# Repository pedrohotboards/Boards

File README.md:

Boards
======

This Repo store the electrical design for all the Hotboards created.

Each folder include, electrical desing, layout, gerber files, docs and the 3d models generated, the following structured
should mandatory. In the near future all the boards presented will created.

Boards
  + \CPUs
    + \8-Bits
      + \Microchip
        + pepper-8m.brd
        + pepper-8m.sch
        + \BOM
        + \gerbers
        + \docs
        + \models
      + \Atmel
      + \Freescale
      + \ST
    + \32-bits/USB
    + \32-bits/USB/ETHERNET
    + \32-bits/USB/ETHERNET/DISPLAY
    + \Low-Power
    + \Multimedia
    + \Linux
    + ...
  + \Accesorios
    + \Comunicaciones
      + \USB-Uart
      + ...
  + \Sensores
    + \Temperatura
    + \Acelerometro
    + \Giroscopio
    + \Compass
    + ...
  + \Almacenamiento
    + \Eeprom
    + \Flash
    + \SD
    + ...
  + \Interruptores
    + \Teclado Matricial
    + \Joystick
    + \DIPs
    + ...
  + \Wireless
    + \WiFi
    + \ZigBee
    + \Bluetooth
    + ...
  + \Displays
    + \Leds
    + \RGBs
    + \LCD
    + \OLED
    + \7Segmentos 
    + ...

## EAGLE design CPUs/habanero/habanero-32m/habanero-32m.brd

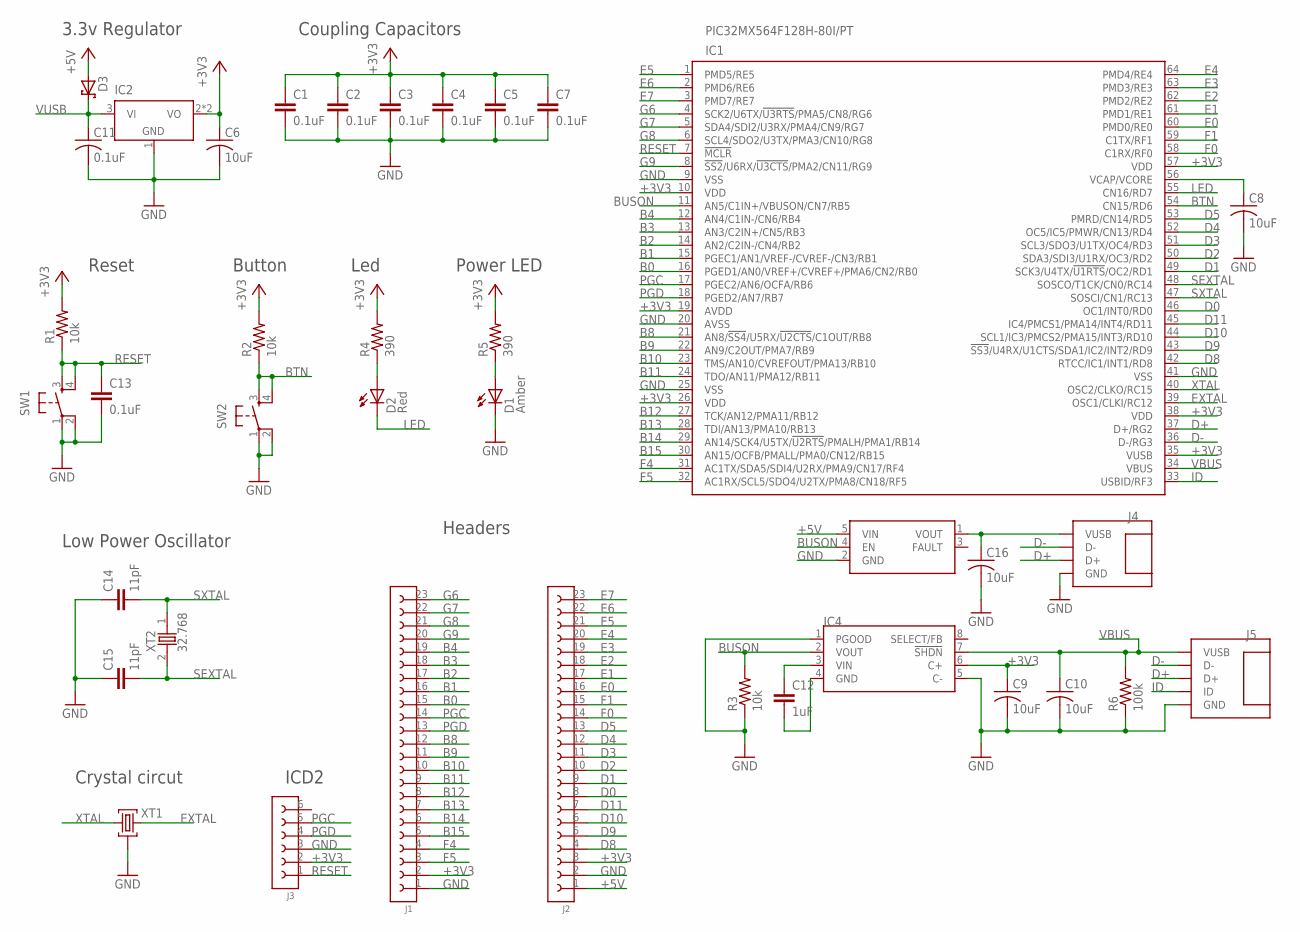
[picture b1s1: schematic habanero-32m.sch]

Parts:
C1, C2, C3, C4, C5, C7, C13: 0.1uF; CAPC0603
C6, C8, C9, C10: 10uF; CAPMP3216-18
C11: 0.1uF; CAPMP3216-18
C12: 1uF; CAPC0805
C14, C15: 11pF; CAPC0603
C16: 10uF; CAPMP3216-18; DIGIKEY 399-8269-2-ND
D1: Amber; D0805
D2: Red; D0805
D3: MBR0530T1G; SOT123160X270-2N
IC1: PIC32MX564F128H-80I/PT; QFP50P1200X1200X100-64N
IC2: LD1117S33TR; SOT230P700X180-4N
IC3: SMTPS2141STR; SOT95P280X100-5M
IC4: MCP1253-33X50I/MS; SOP65P490X109-8M
J1, J2: 61302311121; PHSP254P5842X254X1154-23S
J3: 61300611121; PHSP254P1524X254X1154-6S
J4: 292303-1; USB-A
J5: 1981584-1; USB-MICRO-B
R1, R2, R3: 10k; RESC0603
R4, R5: 390; RESC0603
R6: 100k; RESC0603
SW1, SW2: TL3301NF160QJ; TACT600X600-4J
XT1: AWSCR-12.00CR-C; CERAMIC460X200-3N
XT2: 32.768; CEMIC320X150-2N

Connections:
+3V3: C1.1, C2.1, C3.1, C4.1, C5.1, C6.1, C7.1, C9.1, IC1.10 (VDD), IC1.19 (AVDD), IC1.26 (VDD), IC1.35 (VUSB), IC1.38 (VDD), IC1.57 (VDD), IC2.2 (VO), IC2.4 (VO), IC4.6 (C+), J1.2, J2.3, J3.2, R1.P$2 (2), R2.P$2 (2), R4.P$2 (2), R5.P$2 (2)
+5V: D3.1 (A), IC3.5 (VIN), J2.1
B0: IC1.16 (PGED1/AN0/VREF+/CVREF+/PMA6/CN2/RB0), J1.15
B1: IC1.15 (PGEC1/AN1/VREF-/CVREF-/CN3/RB1), J1.16
B2: IC1.14 (AN2/C2IN-/CN4/RB2), J1.17
B3: IC1.13 (AN3/C2IN+/CN5/RB3), J1.18
B4: IC1.12 (AN4/C1IN-/CN6/RB4), J1.19
B8: IC1.21 (AN8/!SS4!/U5RX/!U2CTS!/C1OUT/RB8), J1.12
B9: IC1.22 (AN9/C2OUT/PMA7/RB9), J1.11
B10: IC1.23 (TMS/AN10/CVREFOUT/PMA13/RB10), J1.10
B11: IC1.24 (TDO/AN11/PMA12/RB11), J1.9
B12: IC1.27 (TCK/AN12/PMA11/RB12), J1.8
B13: IC1.28 (TDI/AN13/PMA10/RB13), J1.7
B14: IC1.29 (AN14/SCK4/U5TX/!U2RTS!/PMALH/PMA1/RB14), J1.6
B15: IC1.30 (AN15/OCFB/PMALL/PMA0/CN12/RB15), J1.5
BTN: IC1.54 (CN15/RD6), R2.P$1 (1), SW2.3 (S), SW2.4 (S1)
BUSON: IC1.11 (AN5/C1IN+/VBUSON/CN7/RB5), IC3.4 (EN), IC4.2 (VOUT), R3.P$2 (2)
D0: IC1.46 (OC1/INT0/RD0), J2.8
D1: IC1.49 (SCK3/U4TX/!U1RTS!/OC2/RD1), J2.9
D2: IC1.50 (SDA3/SDI3/U1RX/OC3/RD2), J2.10
D3: IC1.51 (SCL3/SDO3/U1TX/OC4/RD3), J2.11
D4: IC1.52 (OC5/IC5/PMWR/CN13/RD4), J2.12
D5: IC1.53 (PMRD/CN14/RD5), J2.13
D8: IC1.42 (RTCC/IC1/INT1/RD8), J2.4
D9: IC1.43 (!SS3!/U4RX/U1CTS/SDA1/IC2/INT2/RD9), J2.5
D10: IC1.44 (SCL1/IC3/PMCS2/PMA15/INT3/RD10), J2.6
D11: IC1.45 (IC4/PMCS1/PMA14/INT4/RD11), J2.7
D+: IC1.37 (D+/RG2), J4.2 (D+), J5.3 (D+)
D-: IC1.36 (D-/RG3), J4.3 (D-), J5.2 (D-)
E0: IC1.60 (PMD0/RE0), J2.16
E1: IC1.61 (PMD1/RE1), J2.17
E2: IC1.62 (PMD2/RE2), J2.18
E3: IC1.63 (PMD3/RE3), J2.19
E4: IC1.64 (PMD4/RE4), J2.20
E5: IC1.1 (PMD5/RE5), J2.21
E6: IC1.2 (PMD6/RE6), J2.22
E7: IC1.3 (PMD7/RE7), J2.23
EXTAL: IC1.39 (OSC1/CLKI/RC12), XT1.3
F0: IC1.58 (C1RX/RF0), J2.14
F1: IC1.59 (C1TX/RF1), J2.15
F4: IC1.31 (AC1TX/SDA5/SDI4/U2RX/PMA9/CN17/RF4), J1.4
F5: IC1.32 (AC1RX/SCL5/SDO4/U2TX/PMA8/CN18/RF5), J1.3
G6: IC1.4 (SCK2/U6TX/!U3RTS!/PMA5/CN8/RG6), J1.23
G7: IC1.5 (SDA4/SDI2/U3RX/PMA4/CN9/RG7), J1.22
G8: IC1.6 (SCL4/SDO2/U3TX/PMA3/CN10/RG8), J1.21
G9: IC1.8 (!SS2!/U6RX/!U3CTS!/PMA2/CN11/RG9), J1.20
GND: C1.2, C2.2, C3.2, C4.2, C5.2, C6.2, C7.2, C8.2, C9.2, C10.2, C11.2, C13.2, C14.1, C15.1, C16.2, D1.2 (C), IC1.9 (VSS), IC1.20 (AVSS), IC1.25 (VSS), IC1.41 (VSS), IC2.1 (GND), IC3.2 (GND), IC4.1 (PGOOD), IC4.5 (C-), J1.1, J2.2, J3.3, J4.4 (GND), J5.5 (GND), R3.P$1 (1), R6.P$1 (1), SW1.1, SW1.2 (P1), SW2.1, SW2.2 (P1), XT1.2
ID: IC1.33 (USBID/RF3), J5.4 (ID)
LED: D2.2 (C), IC1.55 (CN16/RD7)
unnamed: C16.1, IC3.1 (VOUT), J4.1 (VUSB)
unnamed: C12.1, IC4.3 (VIN)
unnamed: D1.1 (A), R5.P$1 (1)
unnamed: D2.1 (A), R4.P$1 (1)
unnamed: C12.2, IC4.4 (GND)
unnamed: C8.1, IC1.56 (VCAP/VCORE)
PGC: IC1.17 (PGEC2/AN6/OCFA/RB6), J1.14, J3.5
PGD: IC1.18 (PGED2/AN7/RB7), J1.13, J3.4
RESET: C13.1, IC1.7 (!MCLR), J3.1, R1.P$1 (1), SW1.3 (S), SW1.4 (S1)
SEXTAL: C15.2, IC1.48 (SOSCO/T1CK/CN0/RC14), XT2.2 (1)
SXTAL: C14.2, IC1.47 (SOSCI/CN1/RC13), XT2.1 (2)
VBUS: C10.1, IC1.34 (VBUS), IC4.7 (!SHDN), J5.1 (VUSB), R6.P$2 (2)
VUSB: C11.1, D3.2 (C), IC2.3 (VI)
XTAL: IC1.40 (OSC2/CLKO/RC15), XT1.1

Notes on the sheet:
Coupling Capacitors
3.3v Regulator
Reset
Led
Button
Power LED
Headers
Low Power Oscillator
Crystal circut
ICD2

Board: 2 copper layers, 38 parts (1 on the bottom side), 63 nets, no tracks yet.

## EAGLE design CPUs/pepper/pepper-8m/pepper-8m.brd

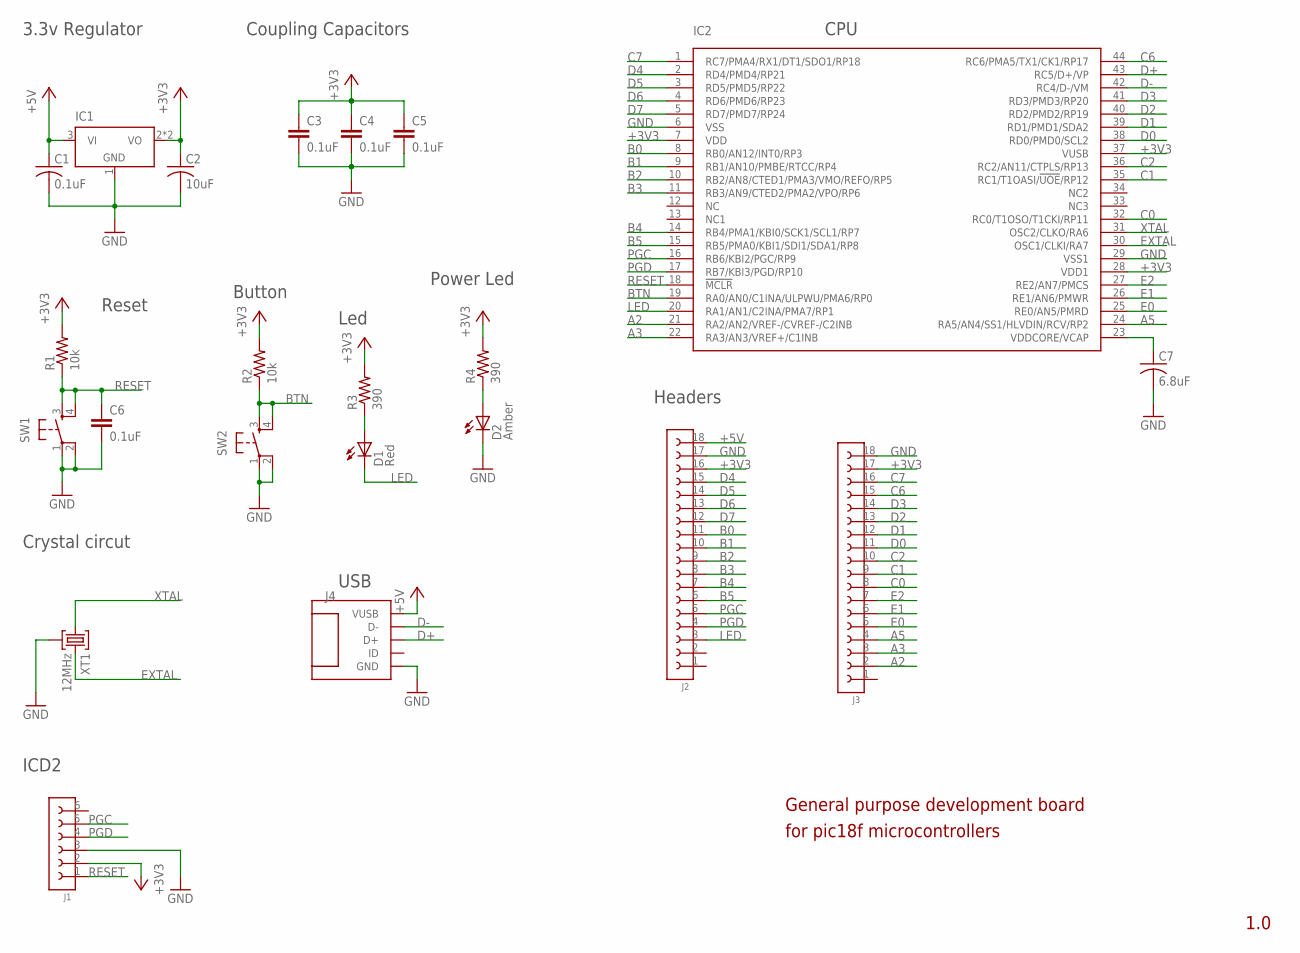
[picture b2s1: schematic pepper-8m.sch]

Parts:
C1: 0.1uF; CAPMP3216-18
C2: 10uF; CAPMP3216-18
C3, C4, C5: 0.1uF; CAPC0603
C6: 0.1uF; CAPC0603; DIGIKEY 399-1100-2-ND
C7: 6.8uF; CAPMP3216-18
D1: Red; D0805
D2: Amber; D0805
IC1: LD1117S33TR; SOT230P700X180-4N
IC2: PIC18F45J50-I/PT'; TQFP80P1200X1200X100-44N
J1: 61300611121; PHSP254P1524X254X1154-6S
J2, J3: 61301811121; PHSP254P4572X254X1154-18S
J4: -1734035-1; USB-MINIB-SMD+SMD+RET
R1, R2: 10k; RESC0603
R3, R4: 390; RESC0603
SW1, SW2: TL3301NF160QJ; TACT600X600-4J
XT1: 12MHz; CERAMIC460X200-3N

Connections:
+3V3: C2.1, C3.1, C4.1, C5.1, IC1.2 (VO), IC1.4 (VO), IC2.7 (VDD), IC2.28 (VDD1), IC2.37 (VUSB), J1.2, J2.16, J3.17, R1.P$2 (2), R2.P$2 (2), R3.P$2 (2), R4.P$2 (2)
+5V: C1.1, IC1.3 (VI), J2.18, J4.1 (VUSB)
A2: IC2.21 (RA2/AN2/VREF-/CVREF-/C2INB), J3.2
A3: IC2.22 (RA3/AN3/VREF+/C1INB), J3.3
A5: IC2.24 (RA5/AN4/SS1/HLVDIN/RCV/RP2), J3.4
B0: IC2.8 (RB0/AN12/INT0/RP3), J2.11
B1: IC2.9 (RB1/AN10/PMBE/RTCC/RP4), J2.10
B2: IC2.10 (RB2/AN8/CTED1/PMA3/VMO/REFO/RP5), J2.9
B3: IC2.11 (RB3/AN9/CTED2/PMA2/VPO/RP6), J2.8
B4: IC2.14 (RB4/PMA1/KBI0/SCK1/SCL1/RP7), J2.7
B5: IC2.15 (RB5/PMA0/KBI1/SDI1/SDA1/RP8), J2.6
BTN: IC2.19 (RA0/AN0/C1INA/ULPWU/PMA6/RP0), R2.P$1 (1), SW2.3 (S), SW2.4 (S1)
C0: IC2.32 (RC0/T1OSO/T1CKI/RP11), J3.8
C1: IC2.35 (RC1/T1OASI/!UOE!/RP12), J3.9
C2: IC2.36 (RC2/AN11/CTPLS/RP13), J3.10
C6: IC2.44 (RC6/PMA5/TX1/CK1/RP17), J3.15
C7: IC2.1 (RC7/PMA4/RX1/DT1/SDO1/RP18), J3.16
D0: IC2.38 (RD0/PMD0/SCL2), J3.11
D1: IC2.39 (RD1/PMD1/SDA2), J3.12
D2: IC2.40 (RD2/PMD2/RP19), J3.13
D3: IC2.41 (RD3/PMD3/RP20), J3.14
D4: IC2.2 (RD4/PMD4/RP21), J2.15
D5: IC2.3 (RD5/PMD5/RP22), J2.14
D6: IC2.4 (RD6/PMD6/RP23), J2.13
D7: IC2.5 (RD7/PMD7/RP24), J2.12
D+: IC2.43 (RC5/D+/VP), J4.3 (D+)
D-: IC2.42 (RC4/D-/VM), J4.2 (D-)
E0: IC2.25 (RE0/AN5/PMRD), J3.5
E1: IC2.26 (RE1/AN6/PMWR), J3.6
E2: IC2.27 (RE2/AN7/PMCS), J3.7
EXTAL: IC2.30 (OSC1/CLKI/RA7), XT1.3
GND: C1.2, C2.2, C3.2, C4.2, C5.2, C6.2, C7.2, D2.2 (C), IC1.1 (GND), IC2.6 (VSS), IC2.29 (VSS1), J1.3, J2.17, J3.18, J4.5 (GND), SW1.1, SW1.2 (P1), SW2.1, SW2.2 (P1), XT1.2
LED: D1.2 (C), IC2.20 (RA1/AN1/C2INA/PMA7/RP1), J2.3
unnamed: D1.1 (A), R3.P$1 (1)
unnamed: C7.1, IC2.23 (VDDCORE/VCAP)
unnamed: D2.1 (A), R4.P$1 (1)
PGC: IC2.16 (RB6/KBI2/PGC/RP9), J1.5, J2.5
PGD: IC2.17 (RB7/KBI3/PGD/RP10), J1.4, J2.4
RESET: C6.1, IC2.18 (!MCLR), J1.1, R1.P$1 (1), SW1.3 (S), SW1.4 (S1)
XTAL: IC2.31 (OSC2/CLKO/RA6), XT1.1

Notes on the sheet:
General purpose development board
3.3v Regulator
Crystal circut
CPU
Reset
Led
Button
USB
Headers
ICD2
Coupling Capacitors
1.0
for pic18f microcontrollers
Power Led

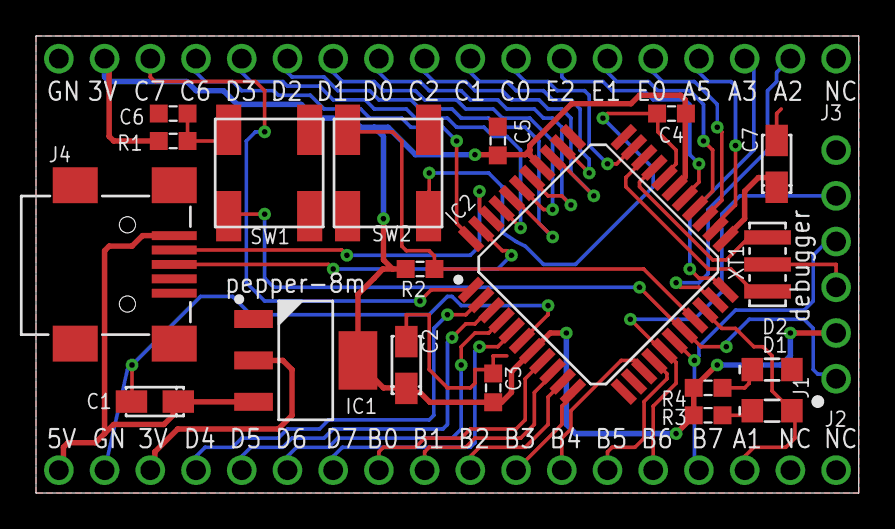
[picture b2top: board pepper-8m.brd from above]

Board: 2 copper layers, 45.7 x 25.4 mm, 22 parts (0 on the bottom side), 40 nets.

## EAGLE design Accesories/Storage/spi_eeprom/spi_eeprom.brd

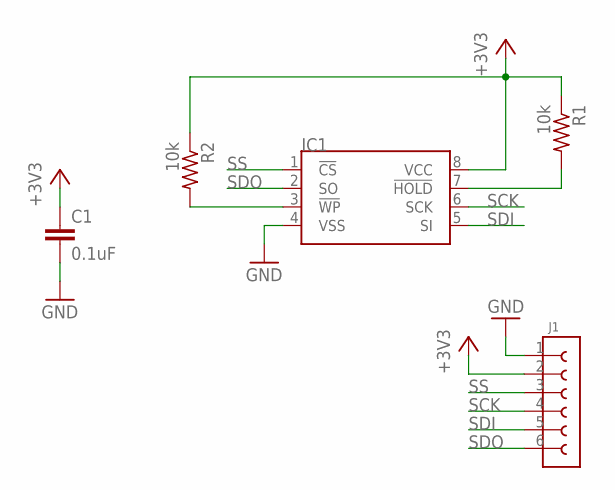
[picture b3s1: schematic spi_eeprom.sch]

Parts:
C1: 0.1uF; CAPC0603
IC1: 25LC320A-I/SN; SOIC127P600X175-8N
J1: 61300611121; PHSP254P1524X254X1154-6S
R1, R2: 10k; RESC0603

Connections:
+3V3: C1.1, IC1.8 (VCC), J1.2, R1.P$1 (1), R2.P$1 (1)
GND: C1.2, IC1.4 (VSS), J1.1
unnamed: IC1.3 (!WP), R2.P$2 (2)
unnamed: IC1.7 (!HOLD), R1.P$2 (2)
SCK: IC1.6 (SCK), J1.4
SDI: IC1.5 (SI), J1.5
SDO: IC1.2 (SO), J1.6
SS: IC1.1 (!CS), J1.3

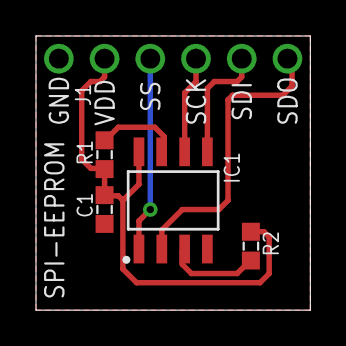
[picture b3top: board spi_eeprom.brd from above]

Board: 2 copper layers, 15.2 x 15.2 mm, 5 parts (0 on the bottom side), 8 nets.

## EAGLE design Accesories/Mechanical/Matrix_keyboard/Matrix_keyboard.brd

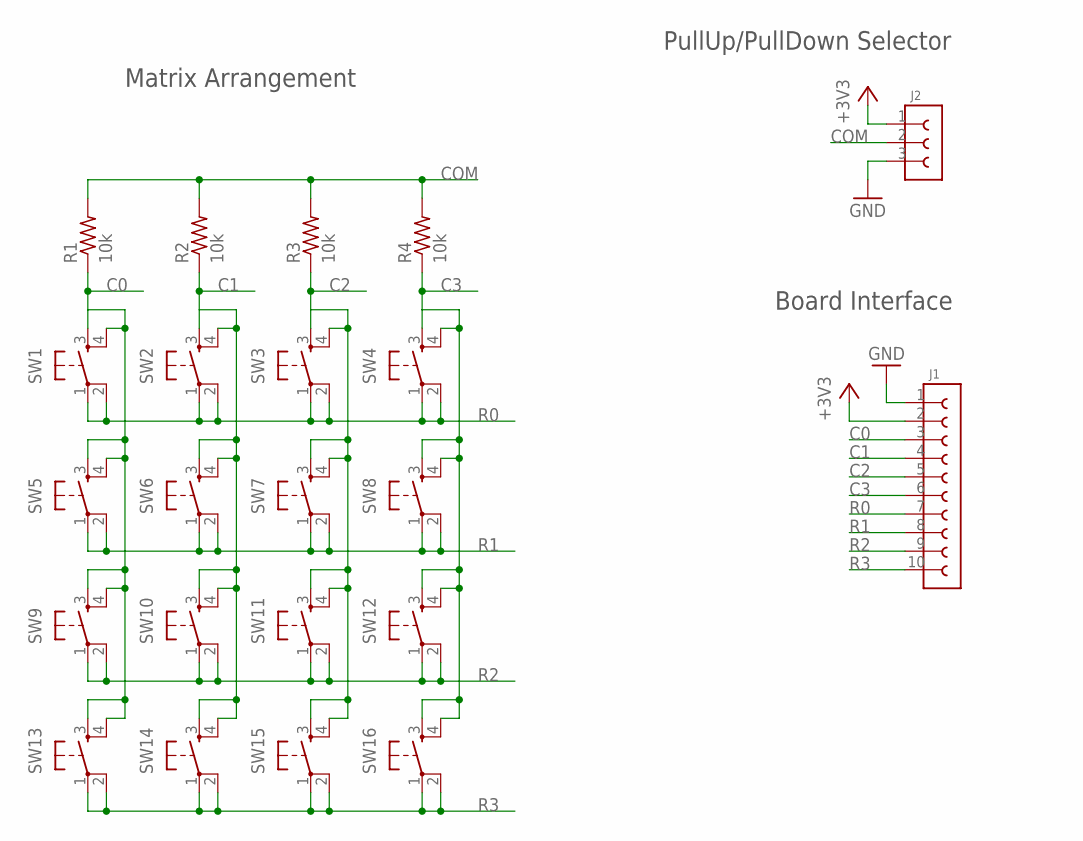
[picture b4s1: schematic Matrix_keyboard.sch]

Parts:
J1: 61301011121; PHSP254P2540X254X1154-10S
J2: 61300311121; PHSP254P762X254X1154-3S
R1, R2, R3, R4: 10k; RESC0603
SW1, SW2, SW3, SW4, SW5, SW6, SW7, SW8, SW9, SW10, SW11, SW12, SW13, SW14, SW15, SW16: TL3301NF160QJ; TACT600X600-4J

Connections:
+3V3: J1.2, J2.1
C0: J1.3, R1.P$1 (1), SW1.3 (S), SW1.4 (S1), SW5.3 (S), SW5.4 (S1), SW9.3 (S), SW9.4 (S1), SW13.3 (S), SW13.4 (S1)
C1: J1.4, R2.P$1 (1), SW2.3 (S), SW2.4 (S1), SW6.3 (S), SW6.4 (S1), SW10.3 (S), SW10.4 (S1), SW14.3 (S), SW14.4 (S1)
C2: J1.5, R3.P$1 (1), SW3.3 (S), SW3.4 (S1), SW7.3 (S), SW7.4 (S1), SW11.3 (S), SW11.4 (S1), SW15.3 (S), SW15.4 (S1)
C3: J1.6, R4.P$1 (1), SW4.3 (S), SW4.4 (S1), SW8.3 (S), SW8.4 (S1), SW12.3 (S), SW12.4 (S1), SW16.3 (S), SW16.4 (S1)
COM: J2.2, R1.P$2 (2), R2.P$2 (2), R3.P$2 (2), R4.P$2 (2)
GND: J1.1, J2.3
R0: J1.7, SW1.1, SW1.2 (P1), SW2.1, SW2.2 (P1), SW3.1, SW3.2 (P1), SW4.1, SW4.2 (P1)
R1: J1.8, SW5.1, SW5.2 (P1), SW6.1, SW6.2 (P1), SW7.1, SW7.2 (P1), SW8.1, SW8.2 (P1)
R2: J1.9, SW9.1, SW9.2 (P1), SW10.1, SW10.2 (P1), SW11.1, SW11.2 (P1), SW12.1, SW12.2 (P1)
R3: J1.10, SW13.1, SW13.2 (P1), SW14.1, SW14.2 (P1), SW15.1, SW15.2 (P1), SW16.1, SW16.2 (P1)

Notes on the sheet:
Matrix Arrangement
Board Interface
PullUp/PullDown Selector

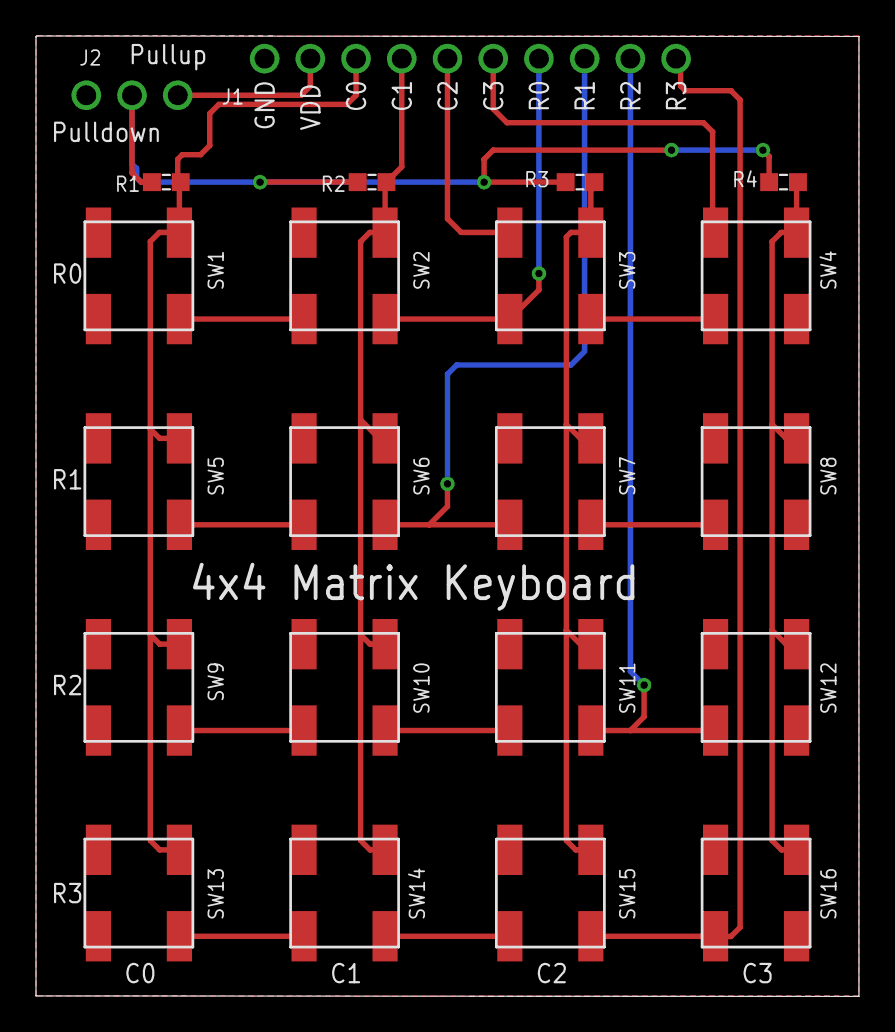
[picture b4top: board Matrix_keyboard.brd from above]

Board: 2 copper layers, 45.7 x 53.4 mm, 22 parts (0 on the bottom side), 11 nets.

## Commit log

2013-04-06 matrix keyboard board
    4x4 keyboard with pullup and pulldown selector
2013-04-06 spi eeprom board
2013-04-06 pepper-8m board
    8bit board with microchip CPU
    Ver1.0
2013-04-06 habanero board
    This is not a final version, minor traces left
2013-04-06 esto solo fue una prueba
    rutee una inea dummy
2013-04-16 Accesory board usb-uart uploaded for the firt time
    this is only the beta version
2013-04-16 rgb led and leds accesory boards uploaded for the first time
    this board are only in beta vesion
2013-04-16 temp sensor board uploaded for the first time
    this is only the beta version
2013-04-16 modificaciones en esquematico
    - se cambiaron los pin headers de 24 a 23 posiciones, para dejar mas
    espacio libre al conector usb on-the-go,
    - se corrigio un error de conexion en el conector para el pickit3
    -se generaron nuevos modelos ya con pin headers
2013-04-16 se creo el esquematico de la nueva tarjeta de 32 bits con ehternet
    version beta, los modelos gneraos son solo para dar una idea de un
    posible placement
2013-05-27 this is version 0.2
    the board is only 0.1" shorter and the silscreeen was corected in oreder
    o add part numbers
2013-06-02 modify resonator part
    unrute all
